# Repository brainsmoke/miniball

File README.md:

Miniball
========

Foldable PCB LED ball

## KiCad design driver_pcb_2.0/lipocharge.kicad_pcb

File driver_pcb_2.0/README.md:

driverpcb 2.0
=========

Circuit design derived from Travis Goodspeed's Goodwatch project,
replacing the CC430F6137 with the smaller footprint CC430F5137:

https://github.com/travisgoodspeed/goodwatch

Lipo charging/load decoupling part of the circuit adapted from:

http://blog.zakkemble.co.uk/a-lithium-battery-charger-with-load-sharing/

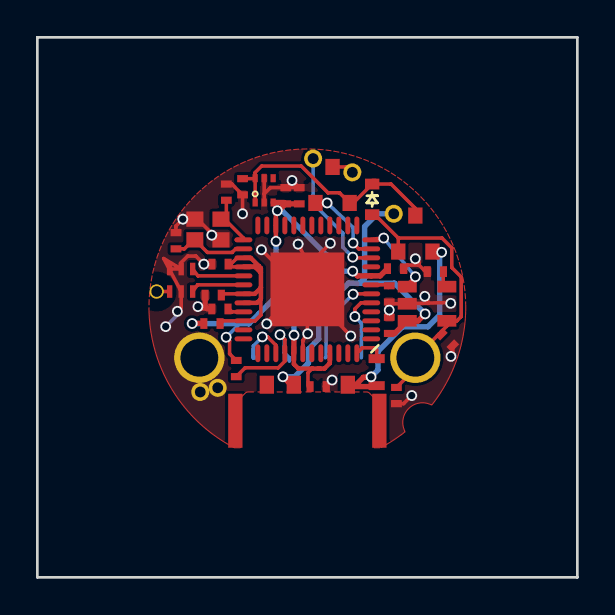
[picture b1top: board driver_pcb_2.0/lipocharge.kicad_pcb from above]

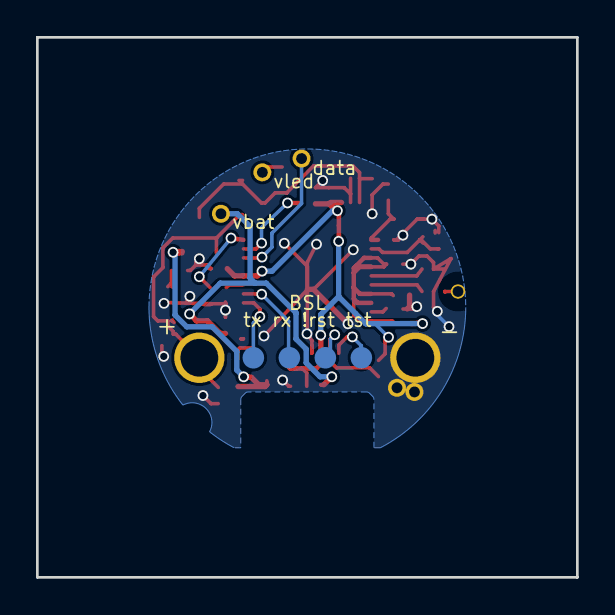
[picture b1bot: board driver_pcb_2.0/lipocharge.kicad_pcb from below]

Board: 2 copper layers, 30.0 x 30.0 mm, 36 parts (3 on the bottom side), 24 nets.

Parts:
ANT1: Conn_01x01; small_hole
C1, C3, C4, C6, C7, C9, C10: 100n; C_0402_NoSilk
C2, C5: 1u; C_0402_NoSilk
C8: 0.47u; C_0402_NoSilk
C11, C12: 19pF; C_0402_NoSilk
D1: D_Schottky; D_0603
D2: VDROP; R0603
DATALED1: -; small_hole
GND1: CONN_01X01; Pin_Header_Straight_1x01_Pitch2.54mm
GNDBATT1: -; small_hole
GNDLED1: -; small_hole
J3: BSL; Pin_Header_Straight_1x06_Pitch1.00mm
L1: L; C_0402_NoSilk
Q1, Q2: AO3401-P Mosfet; SOT-23
R1: 15K; R_0402_NoSilk
R2, R3, R4: 56K; R_0402_NoSilk
SW1: CONN_01X03; Conn-3
U1: MCP73831; SOT-23-5
U2: CC430F513x
U3: ncp170axv330; sot-563
U4: 0433bm15a0001
VBATT1: +; small_hole
VIN1: CONN_01X01; Pin_Header_Straight_1x01_Pitch2.54mm
VLED1: -; small_hole
X1: FA128

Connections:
/3V3: C4.1, C5.1, C6.1, C7.1, L1.1, R2.1, U2.8, U2.22, U2.41, U2.45, U3.3
/!RST: J3.3, R2.2, U2.40
/BSL_RX: J3.2, U2.6
/BSL_TX: J3.1, U2.5
/DOUT: DATALED1.1, U2.10
/PROG: R1.2, U1.5
/PWRSW: Q2.1, U2.11
/RF_N: U2.30, U4.3
/RF_P: U2.29, U4.4
/RF_XIN: C11.1, U2.25, X1.1
/RF_XOUT: C12.1, U2.26, X1.3
/STAT: U1.1, U2.12
/TEST: J3.4, U2.39
/VADC: D2.1, U2.48
/VBAT: C3.1, SW1.2, U1.3, VBATT1.1
/VBATSW: D2.2, Q1.2, SW1.3
/VCC: C2.1, D1.1, Q1.3, Q2.2, U3.1, U3.6
/VIN: C1.1, D1.2, Q1.1, R3.2, U1.4, VIN1.1
/VLED: Q2.3, VLED1.1
GND: C1.2, C2.2, C3.2, C4.2, C5.2, C6.2, C7.2, C8.2, C9.1, C10.1, C11.2, C12.2, GND1.1, GNDBATT1.1, GNDLED1.1, R1.1, R3.1, R4.2, U1.2, U2.42, U2.49, U3.2, U3.5, U4.2, U4.5, U4.6, X1.2, X1.4
unnamed: ANT1.1, U4.1
unnamed: C8.1, U2.7
unnamed: C9.2, C10.2, L1.2, U2.27, U2.28, U2.31, U2.32, U2.34
unnamed: R4.1, U2.33

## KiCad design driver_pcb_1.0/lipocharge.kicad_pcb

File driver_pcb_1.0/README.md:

driverpcb
=========

Single layer redesign of v0.1

Circuit adapted from

http://blog.zakkemble.co.uk/a-lithium-battery-charger-with-load-sharing/

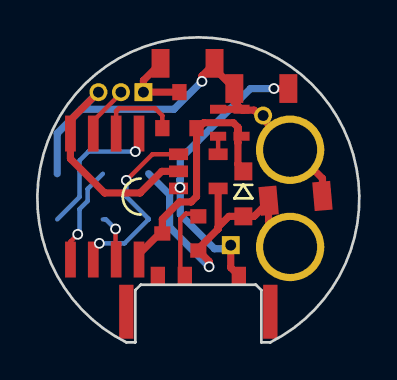
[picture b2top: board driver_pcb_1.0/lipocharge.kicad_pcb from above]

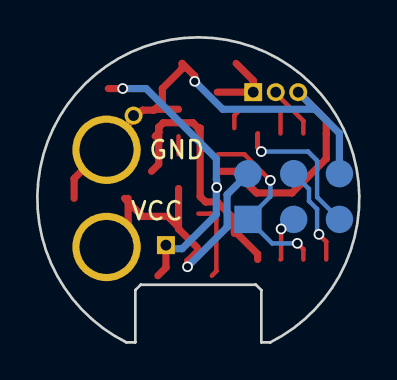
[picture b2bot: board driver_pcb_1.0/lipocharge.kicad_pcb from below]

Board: 2 copper layers, 17.9 x 16.9 mm, 16 parts (3 on the bottom side), 13 nets.

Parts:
C1, C2, C3: 4u7; C_1206
C4: 100n; C_0603
CON1: AVR-ISP-6; pin_array_3x2
D1: D_Schottky; SOD-323_HandSoldering
GND: CONN_01X01; Pin_Header_Straight_1x01_Pitch2.54mm
IC1: ATTINY85-S; SO8E
P1: LEDBALL; Pin_Header_Straight_1x03_Pitch2.54mm
P3: BATT; Pin_Header_Straight_1x02_Pitch2.54mm
Q1, Q2: AO2401-P Mosfet; SOT-23
R1: 15K; R_0603
SW1: CONN_01X03; Conn-3
U1: MCP73831; SOT-23-5
VCC: CONN_01X01; Pin_Header_Straight_1x01_Pitch2.54mm

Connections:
/DOUT: IC1.3, P1.2
/MISO: CON1.1, IC1.6, U1.1
/MOSI: CON1.4, IC1.5
/PROG: R1.2, U1.5
/PWRSW: IC1.2, Q2.1
/RST: CON1.5, IC1.1
/SCK: CON1.3, IC1.7
/VBAT: C3.1, P3.1, SW1.3, U1.3
/VCC: C4.1, D1.1, IC1.8, Q1.3, Q2.2
/VIN: C1.1, CON1.2, D1.2, Q1.1, U1.4, VCC.1
/VLED: C2.1, P1.1, Q2.3
GND: C1.2, C2.2, C3.2, C4.2, CON1.6, GND.1, IC1.4, P1.3, P3.2, R1.1, U1.2
unnamed: Q1.2, SW1.2

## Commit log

2017-07-13 combined repo initial commit
2017-07-16 add base shape
2017-07-17 ball base 3d-print
2017-07-17 circuit creds
2017-08-24 charging animation / low power LED power cutoff
2017-08-24 whitespace
2017-08-24 nicer charge animation
2017-08-24 use image if finished ball
2017-08-24 use image of finished ball
2017-09-21 add animation with uball coordinates
2017-09-28 make copy of current pcb
2017-09-28 add battery status indication on startup
2017-09-28 move ball pcb to mini_pcb dir
2017-09-28 add uball
2017-09-28 add uball svg->kicad files
2017-09-28 add design files for uball
2017-09-28 add uball image
2018-06-28 goodwatch based driver pcb
2018-06-28 wire !RST as !RST instead of RST
2018-06-28 Readme
2018-06-28 export fixed ball base to stl
2018-07-28 change voltage measuring circuit to use LED as voltage drop
2019-01-08 Add msp430 code
2020-07-11 I don't remember anymore
2020-07-11 add fire animation for attiny
2020-07-11 add attiny4 code/emulator
2020-07-12 add mit licence
